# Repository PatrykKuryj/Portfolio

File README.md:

# Portfolio
Projekty i pliki, które wykonałem lub byłem częścią zespołu towrzacego daną pracę.

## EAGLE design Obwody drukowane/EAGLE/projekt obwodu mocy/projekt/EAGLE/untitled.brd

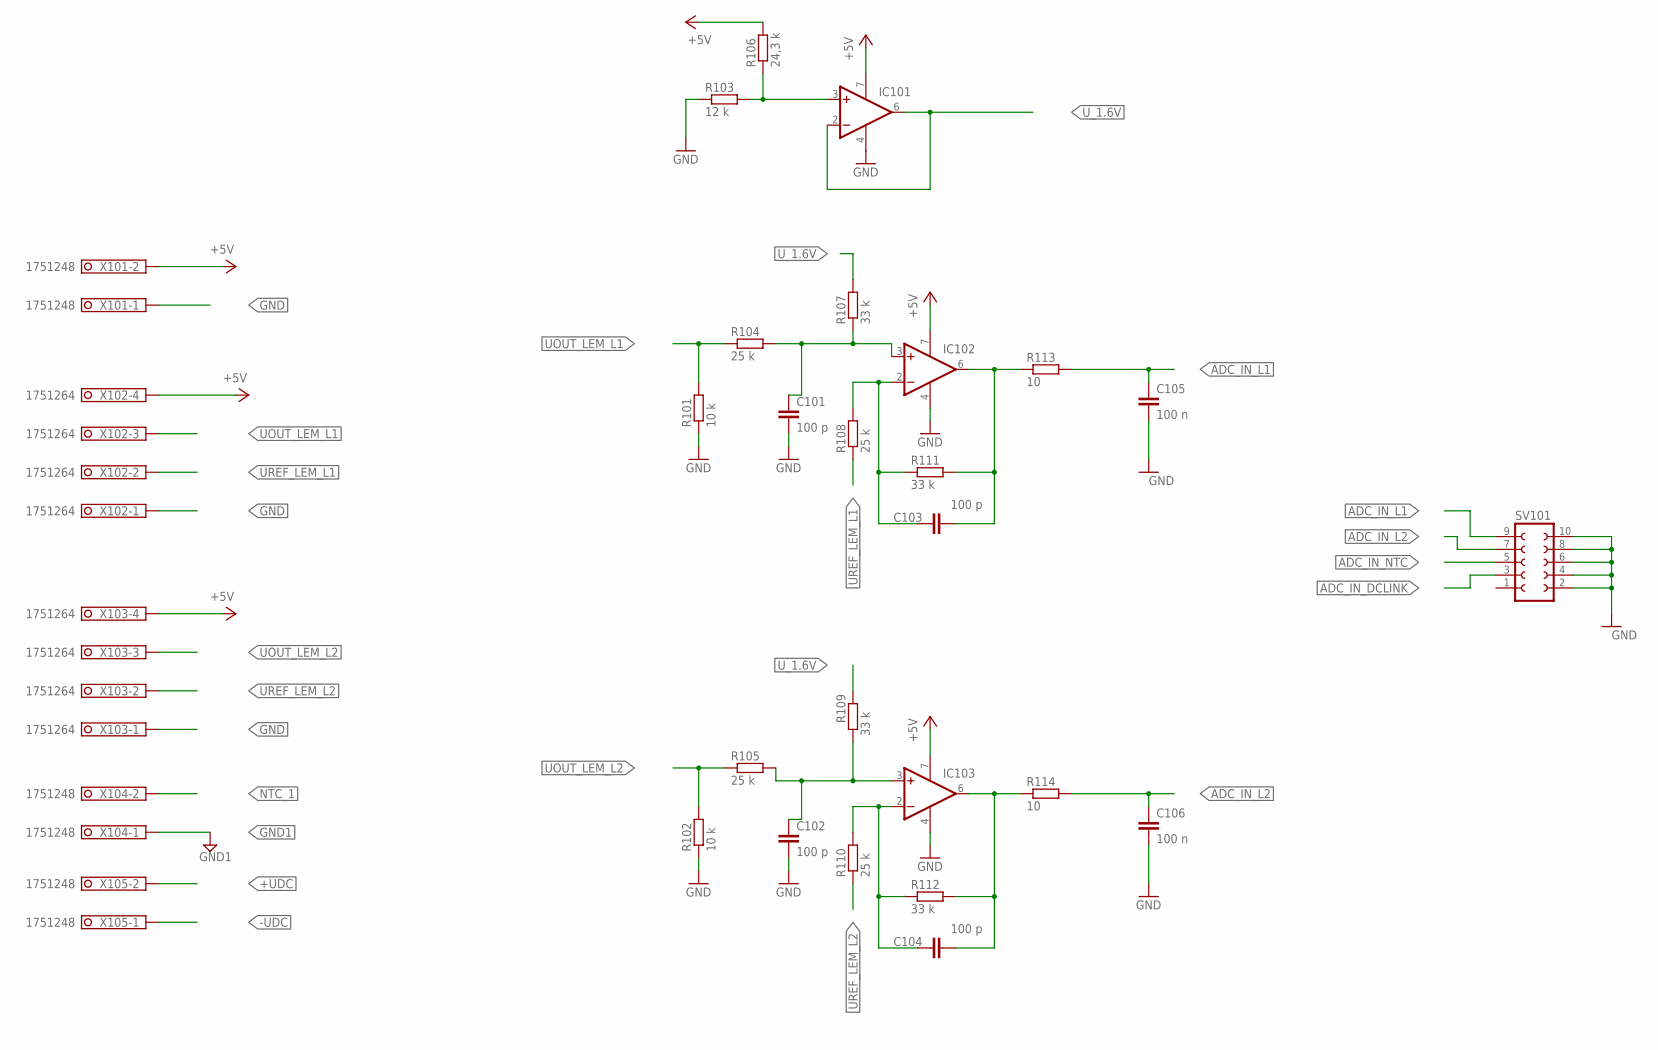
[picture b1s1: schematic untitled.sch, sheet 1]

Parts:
C101, C102, C103, C104: 100 p; C0603
C105, C106: 100 n; C1206
IC101, IC102, IC103: 1AMP_P7+4D; SO08
R101, R102: 10 k; R0402
R103: 12 k; R0402
R104, R105, R108, R110: 25 k; R0402
R106: 24,3 k; R0402
R107, R109, R111, R112: 33 k; R0402
R113, R114: 10; R0402
SV101: FE05-2
X101, X104, X105: 1751248
X102, X103: 1751264

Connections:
+5V: IC101.7 (V+), IC102.7 (V+), IC103.7 (V+), R106.2, X101.2, X102.4, X103.4; also elsewhere on the board
+UDC: X105.2; also elsewhere on the board
-UDC: X105.1; also elsewhere on the board
ADC_IN_DCLINK: SV101.3; also elsewhere on the board
ADC_IN_L1: C105.1, R113.2, SV101.9
ADC_IN_L2: C106.1, R114.2, SV101.7
ADC_IN_NTC: SV101.5; also elsewhere on the board
GND: C101.2, C102.2, C105.2, C106.2, IC101.4 (V-), IC102.4 (V-), IC103.4 (V-), R101.1, R102.1, R103.1, SV101.2, SV101.4, SV101.6, SV101.8, SV101.10, X101.1, X102.1, X103.1; also elsewhere on the board
GND1: X104.1; also elsewhere on the board
unnamed: C104.1, IC103.2 (-IN), R110.2, R112.1
unnamed: C104.2, IC103.6 (OUT), R112.2, R114.1
unnamed: C103.1, IC102.2 (-IN), R108.2, R111.1
unnamed: C103.2, IC102.6 (OUT), R111.2, R113.1
unnamed: IC101.3 (+IN), R103.2, R106.1
unnamed: C102.1, IC103.3 (+IN), R105.2, R109.1
unnamed: C101.1, IC102.3 (+IN), R104.2, R107.1
NTC_1: X104.2; also elsewhere on the board
UOUT_LEM_L1: R101.2, R104.1, X102.3
UOUT_LEM_L2: R102.2, R105.1, X103.3
UREF_LEM_L1: R108.1, X102.2
UREF_LEM_L2: R110.1, X103.2
U_1.6V: IC101.2 (-IN), IC101.6 (OUT), R107.2, R109.2; also elsewhere on the board

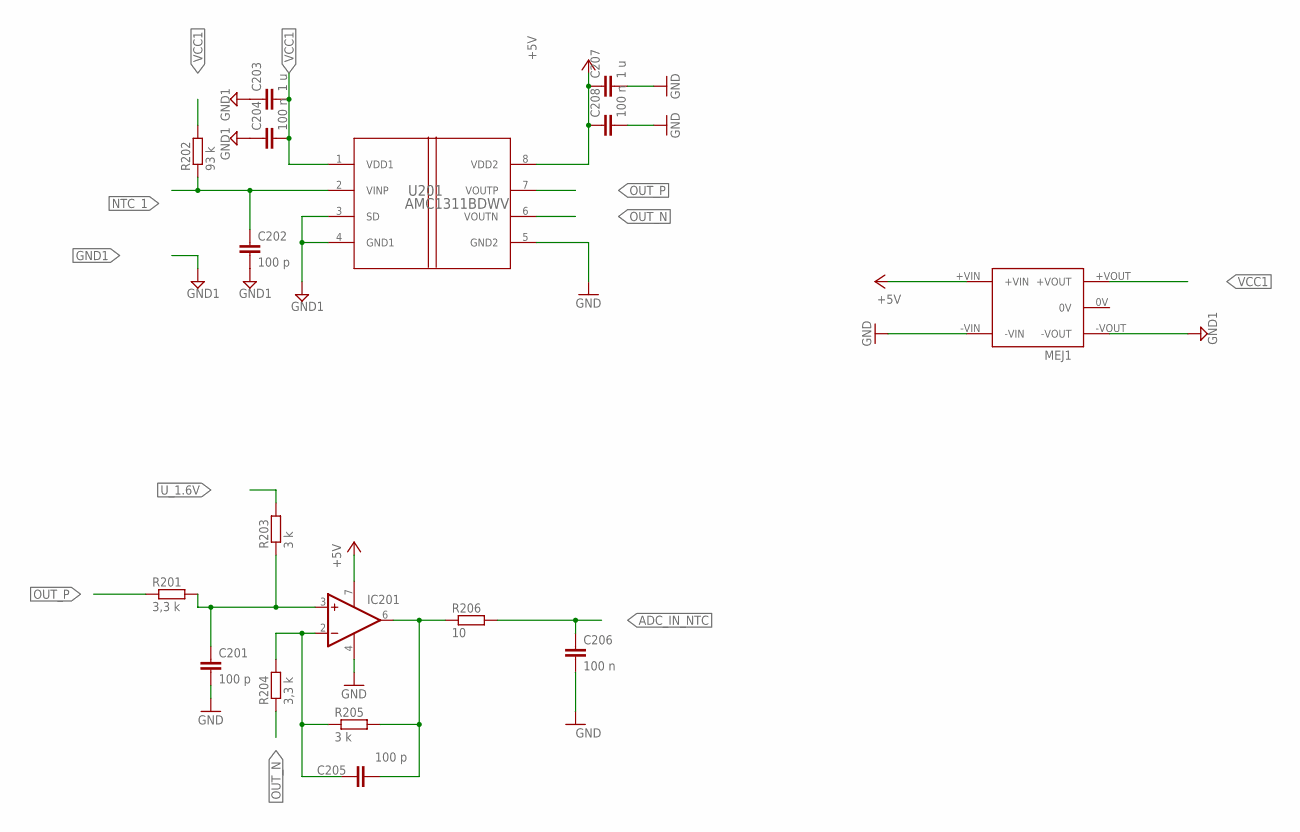
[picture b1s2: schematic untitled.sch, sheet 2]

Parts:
C201, C202, C205: 100 p; C0603
C203, C207: 1 u; C0805
C204, C208: 100 n; C0805
C206: 100 n; C1206
IC201: 1AMP_P7+4D; SO08
MEJ1: MEJ1
R201, R204: 3,3 k; R0402
R202: 93 k; R0402
R203, R205: 3 k; R0402
R206: 10; R0402
U201: AMC1311BDWV; DWV0008A

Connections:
+5V: C207.1, C208.1, IC201.7 (V+), MEJ1.+VIN, U201.8 (VDD2); also elsewhere on the board
ADC_IN_NTC: C206.1, R206.2; also elsewhere on the board
GND: C201.2, C206.2, C207.2, C208.2, IC201.4 (V-), MEJ1.-VIN, U201.5 (GND2); also elsewhere on the board
GND1: C202.2, C203.1, C204.1, MEJ1.-VOUT, U201.3 (SD), U201.4 (GND1); also elsewhere on the board
unnamed: C205.1, IC201.2 (-IN), R204.2, R205.1
unnamed: C205.2, IC201.6 (OUT), R205.2, R206.1
unnamed: C201.1, IC201.3 (+IN), R201.2, R203.1
NTC_1: C202.1, R202.1, U201.2 (VINP); also elsewhere on the board
OUT_N: R204.1, U201.6 (VOUTN)
OUT_P: R201.1, U201.7 (VOUTP)
U_1.6V: R203.2; also elsewhere on the board
VCC1: C203.2, C204.2, MEJ1.+VOUT, R202.2, U201.1 (VDD1); also elsewhere on the board

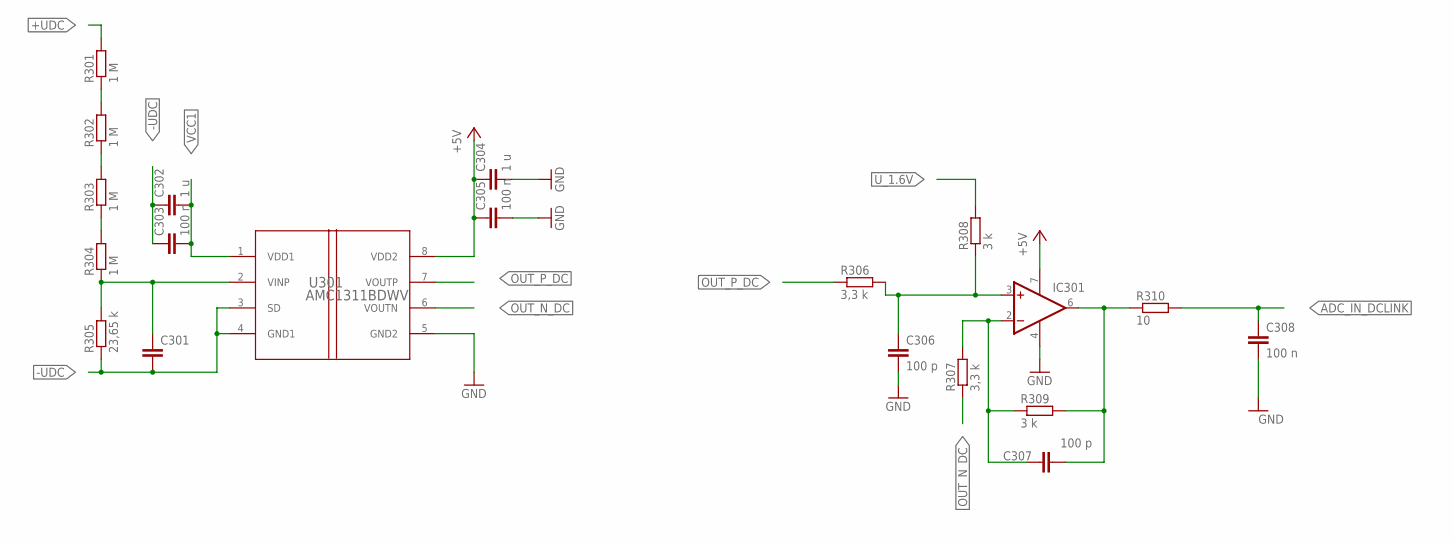
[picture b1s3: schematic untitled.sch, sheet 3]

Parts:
C301, C306, C307: 100 p; C0603
C302, C304: 1 u; C0805
C303, C305: 100 n; C0805
C308: 100 n; C1206
IC301: 1AMP_P7+4D; SO08
R301, R302, R303, R304: 1 M; R0603
R305: 23,65 k; R0603
R306, R307: 3,3 k; R0402
R308, R309: 3 k; R0402
R310: 10; R0402
U301: AMC1311BDWV; DWV0008A

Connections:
+5V: C304.1, C305.1, IC301.7 (V+), U301.8 (VDD2); also elsewhere on the board
+UDC: R301.2; also elsewhere on the board
-UDC: C301.2, C302.1, C303.1, R305.1, U301.3 (SD), U301.4 (GND1); also elsewhere on the board
ADC_IN_DCLINK: C308.1, R310.2; also elsewhere on the board
GND: C304.2, C305.2, C306.2, C308.2, IC301.4 (V-), U301.5 (GND2); also elsewhere on the board
unnamed: R303.1, R304.2
unnamed: R301.1, R302.2
unnamed: C307.1, IC301.2 (-IN), R307.2, R309.1
unnamed: C307.2, IC301.6 (OUT), R309.2, R310.1
unnamed: R302.1, R303.2
unnamed: C306.1, IC301.3 (+IN), R306.2, R308.1
unnamed: C301.1, R304.1, R305.2, U301.2 (VINP)
OUT_N_DC: R307.1, U301.6 (VOUTN)
OUT_P_DC: R306.1, U301.7 (VOUTP)
U_1.6V: R308.2; also elsewhere on the board
VCC1: C302.2, C303.2, U301.1 (VDD1); also elsewhere on the board

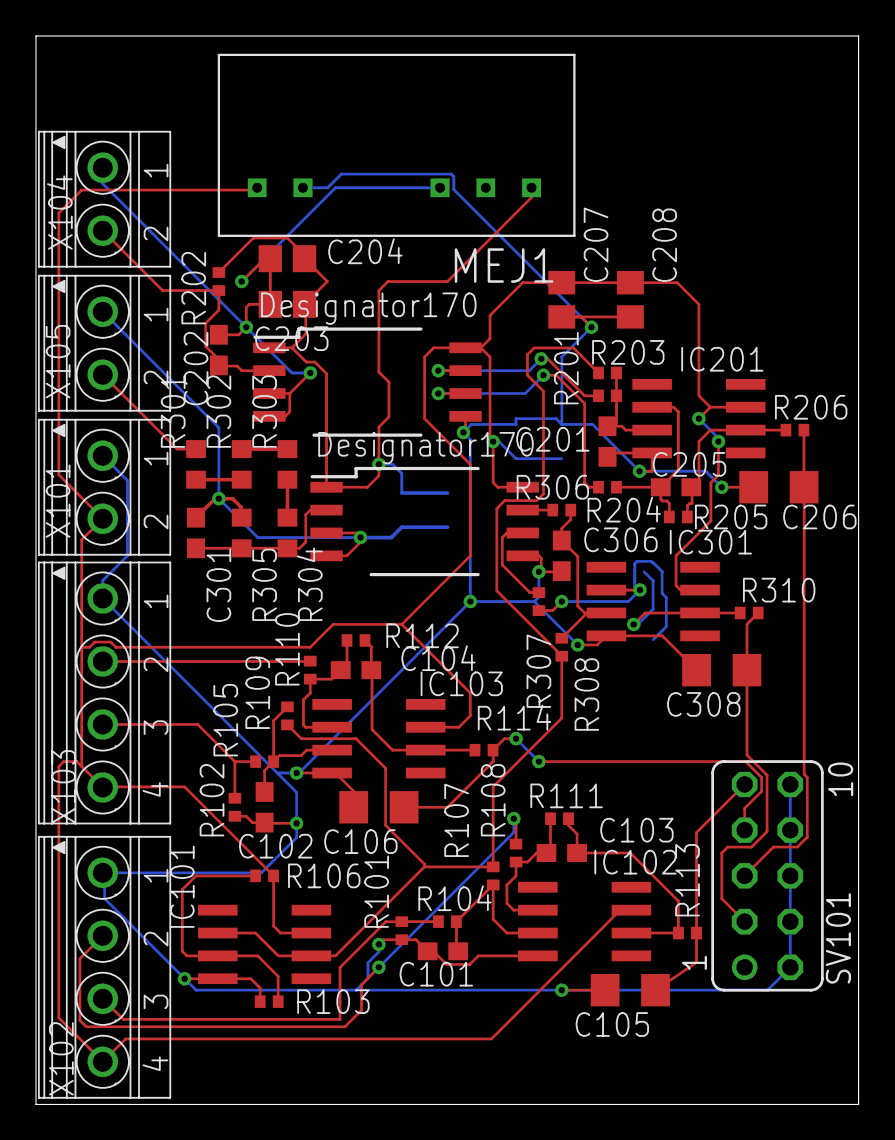
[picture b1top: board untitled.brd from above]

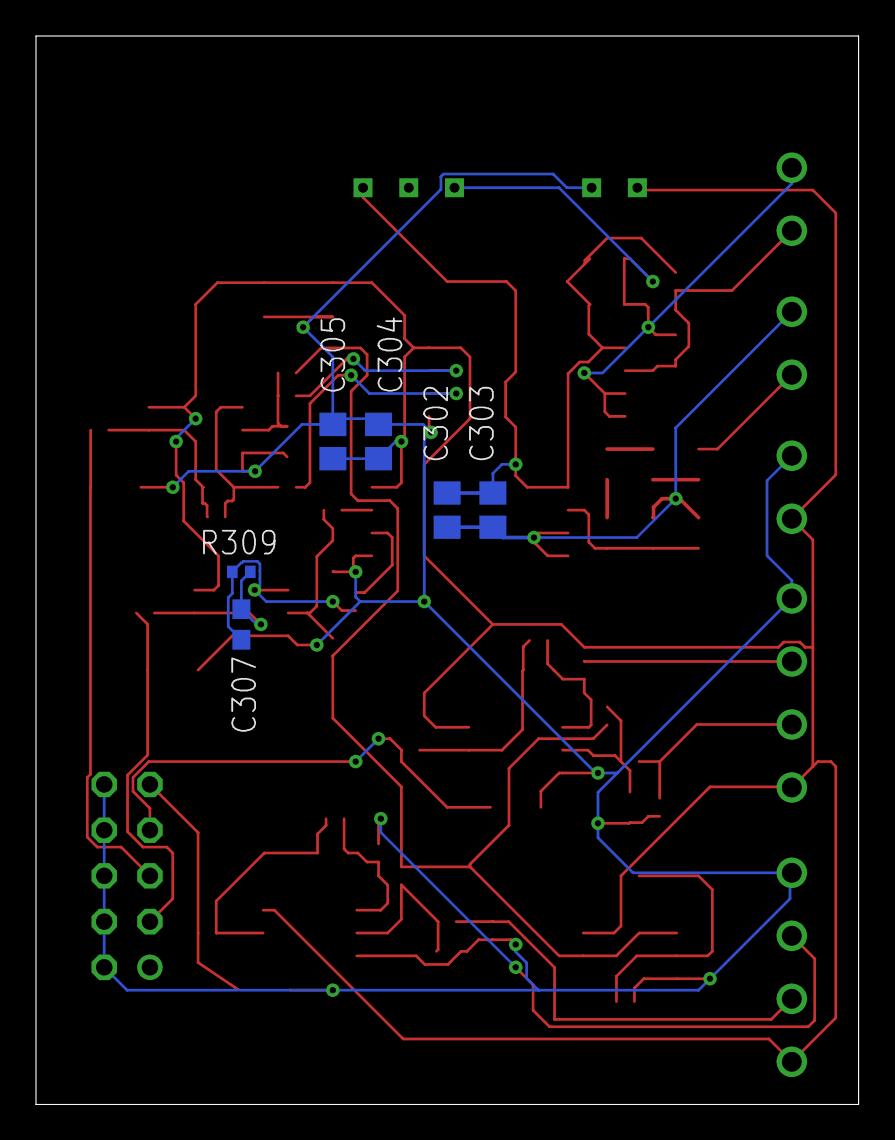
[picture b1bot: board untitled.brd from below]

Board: 2 copper layers, 45.7 x 59.4 mm, 66 parts (6 on the bottom side), 37 nets.

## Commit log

2025-10-30 pliki
2025-11-15 Rename 0012c4b1-6e22-4d83-a482-4652236d3646.jpg to Płytka sterująca hudroponika.jpg
2025-11-15 Rename 6bea2800-5418-42c4-b477-d21b7d99d01a.jpg to płytka sterująca hydroponika przód
2025-11-15 Rename płytka sterująca hydroponika przód to płytka sterująca hydroponika przód.jpg
2025-11-15 Rename Płytka sterująca hudroponika.jpg to Płytka sterująca hydroponika tył.jpg

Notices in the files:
parts and their libraries:
COPYRIGHT: Copyright (C) 2024 Ultra Librarian. All rights reserved.
